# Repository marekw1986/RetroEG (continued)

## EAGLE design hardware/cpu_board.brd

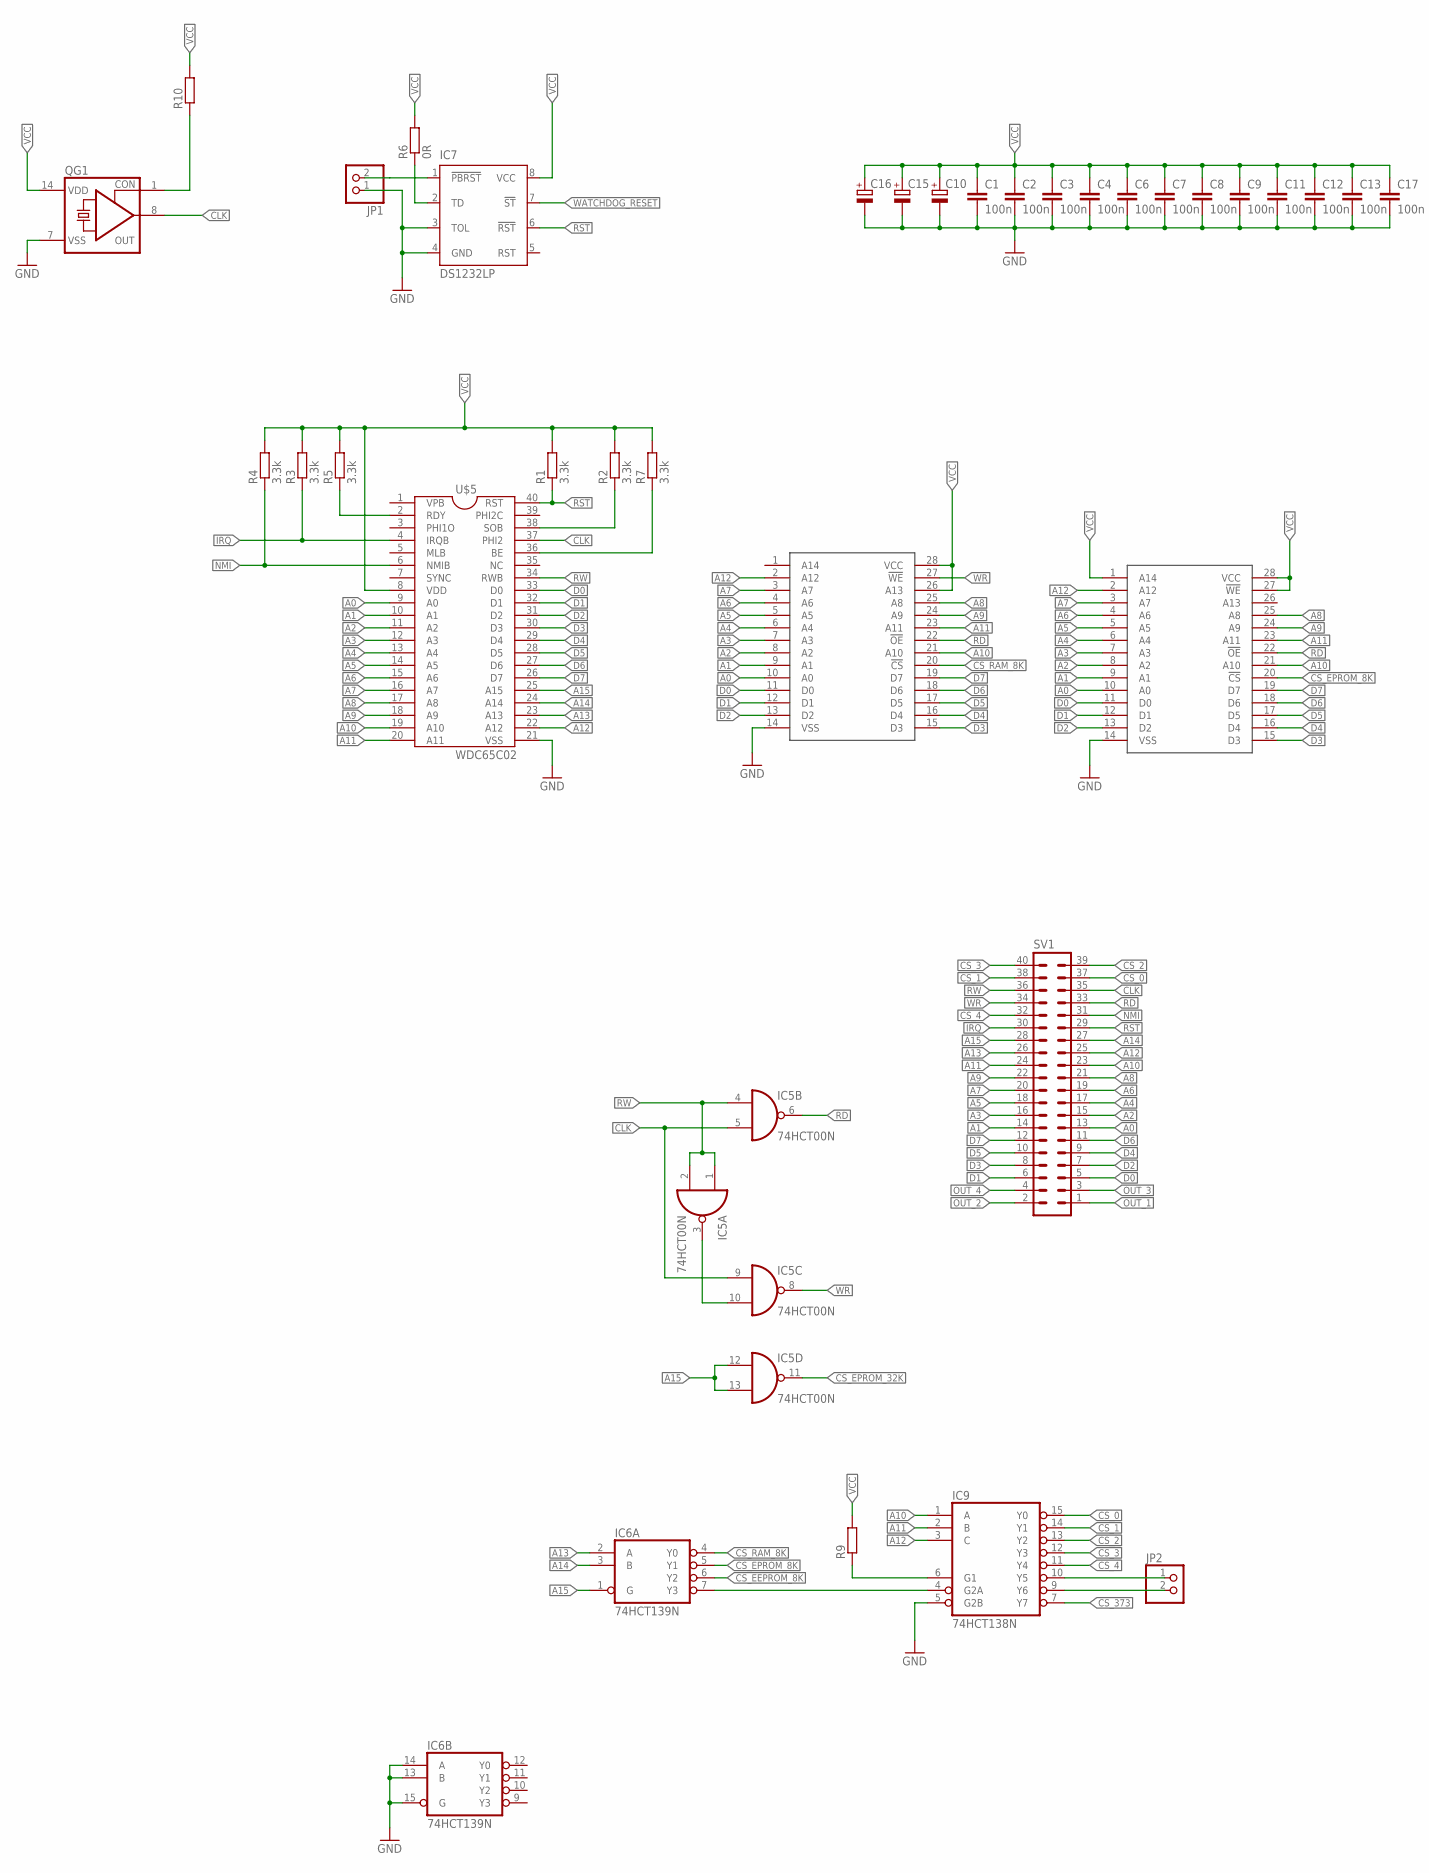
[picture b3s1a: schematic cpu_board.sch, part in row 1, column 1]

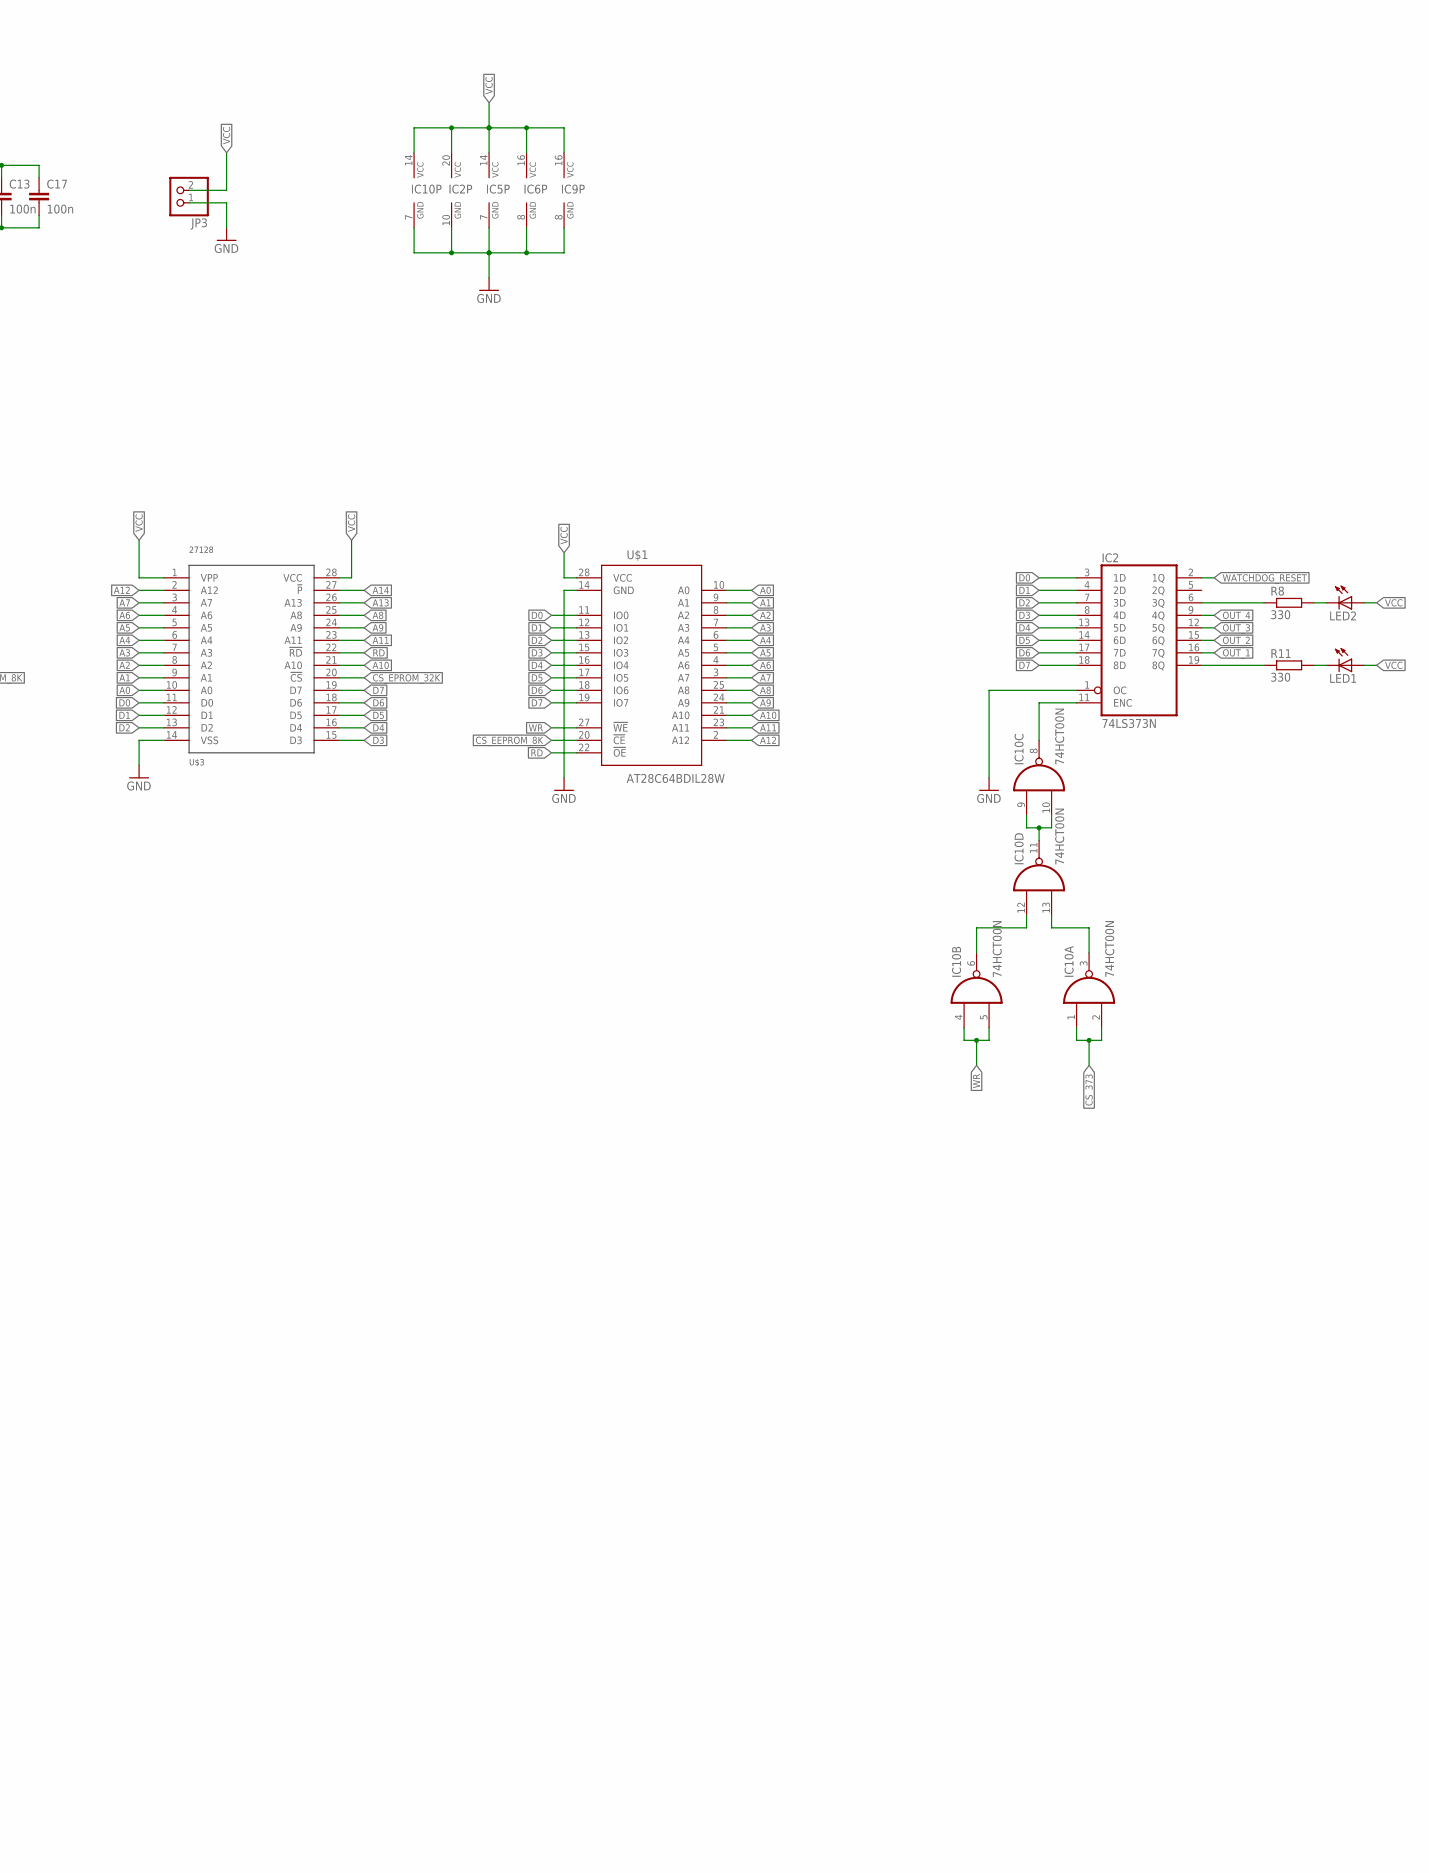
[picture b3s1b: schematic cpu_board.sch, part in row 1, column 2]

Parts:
C1, C2, C3, C4, C6, C7, C8, C9, C17: 100n; C1206
C10: CPOL-EUE5-10.5; E5-10,5
C11, C12, C13: 100n; C0805
C15, C16: CPOL-EUSMCB; SMC_B
IC2: 74LS373N; DIL20
IC5, IC10: 74HCT00N; DIL14
IC6: 74HCT139N; DIL16
IC7: DS1232LP; DIL08
IC9: 74HCT138N; DIL16
JP1, JP2: PINHD-1X2; 1X02
JP3: PINHD-1X2/90; 1X02/90
LED1, LED2: LED5MM
QG1: CRYSTAL_RES-SG51; SG51
R1, R2, R3, R4, R5, R7: 3.3k; R1206
R6: 0R; R1206
R8, R11: 330; R1206
R9: R-EU_0204/7; 0204/7
R10: R-EU_R1206; R1206
SV1: ML40L
U$1: AT28C64BDIL28W; DIL28-6
U$2, U$4: 62256; DIL28-6
U$3: 27128; DIL28
U$5: WDC65C02; DIL40

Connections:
A0: SV1.13, U$1.10 (A0), U$2.10 (A0), U$3.10 (A0), U$4.10 (A0), U$5.9 (A0)
A1: SV1.14, U$1.9 (A1), U$2.9 (A1), U$3.9 (A1), U$4.9 (A1), U$5.10 (A1)
A2: SV1.15, U$1.8 (A2), U$2.8 (A2), U$3.8 (A2), U$4.8 (A2), U$5.11 (A2)
A3: SV1.16, U$1.7 (A3), U$2.7 (A3), U$3.7 (A3), U$4.7 (A3), U$5.12 (A3)
A4: SV1.17, U$1.6 (A4), U$2.6 (A4), U$3.6 (A4), U$4.6 (A4), U$5.13 (A4)
A5: SV1.18, U$1.5 (A5), U$2.5 (A5), U$3.5 (A5), U$4.5 (A5), U$5.14 (A5)
A6: SV1.19, U$1.4 (A6), U$2.4 (A6), U$3.4 (A6), U$4.4 (A6), U$5.15 (A6)
A7: SV1.20, U$1.3 (A7), U$2.3 (A7), U$3.3 (A7), U$4.3 (A7), U$5.16 (A7)
A8: SV1.21, U$1.25 (A8), U$2.25 (A8), U$3.25 (A8), U$4.25 (A8), U$5.17 (A8)
A9: SV1.22, U$1.24 (A9), U$2.24 (A9), U$3.24 (A9), U$4.24 (A9), U$5.18 (A9)
A10: IC9.1 (A), SV1.23, U$1.21 (A10), U$2.21 (A10), U$3.21 (A10), U$4.21 (A10), U$5.19 (A10)
A11: IC9.2 (B), SV1.24, U$1.23 (A11), U$2.23 (A11), U$3.23 (A11), U$4.23 (A11), U$5.20 (A11)
A12: IC9.3 (C), SV1.25, U$1.2 (A12), U$2.2 (A12), U$3.2 (A12), U$4.2 (A12), U$5.22 (A12)
A13: IC6.2 (A), SV1.26, U$3.26 (A13), U$5.23 (A13)
A14: IC6.3 (B), SV1.27, U$3.27 (!P), U$5.24 (A14)
A15: IC5.12 (I0), IC5.13 (I1), IC6.1 (G), SV1.28, U$5.25 (A15)
CLK: IC5.5 (I1), IC5.9 (I0), QG1.8 (OUT), SV1.35, U$5.37 (PHI2)
CS_0: IC9.15 (Y0), SV1.37
CS_1: IC9.14 (Y1), SV1.38
CS_2: IC9.13 (Y2), SV1.39
CS_3: IC9.12 (Y3), SV1.40
CS_4: IC9.11 (Y4), SV1.32
CS_373: IC9.7 (Y7), IC10.1 (I0), IC10.2 (I1)
CS_EEPROM_8K: IC6.6 (Y2), U$1.20 (!CE)
CS_EPROM_8K: IC6.5 (Y1), U$2.20 (!CS)
CS_EPROM_32K: IC5.11 (O), U$3.20 (!CS)
CS_RAM_8K: IC6.4 (Y0), U$4.20 (!CS)
D0: IC2.3 (1D), SV1.5, U$1.11 (IO0), U$2.11 (D0), U$3.11 (D0), U$4.11 (D0), U$5.33 (D0)
D1: IC2.4 (2D), SV1.6, U$1.12 (IO1), U$2.12 (D1), U$3.12 (D1), U$4.12 (D1), U$5.32 (D1)
D2: IC2.7 (3D), SV1.7, U$1.13 (IO2), U$2.13 (D2), U$3.13 (D2), U$4.13 (D2), U$5.31 (D2)
D3: IC2.8 (4D), SV1.8, U$1.15 (IO3), U$2.15 (D3), U$3.15 (D3), U$4.15 (D3), U$5.30 (D3)
D4: IC2.13 (5D), SV1.9, U$1.16 (IO4), U$2.16 (D4), U$3.16 (D4), U$4.16 (D4), U$5.29 (D4)
D5: IC2.14 (6D), SV1.10, U$1.17 (IO5), U$2.17 (D5), U$3.17 (D5), U$4.17 (D5), U$5.28 (D5)
D6: IC2.17 (7D), SV1.11, U$1.18 (IO6), U$2.18 (D6), U$3.18 (D6), U$4.18 (D6), U$5.27 (D6)
D7: IC2.18 (8D), SV1.12, U$1.19 (IO7), U$2.19 (D7), U$3.19 (D7), U$4.19 (D7), U$5.26 (D7)
GND: C1.2, C2.2, C3.2, C4.2, C6.2, C7.2, C8.2, C9.2, C10.-, C11.2, C12.2, C13.2, C15.-, C16.-, C17.2, IC2.1 (OC), IC2.10 (GND), IC5.7 (GND), IC6.8 (GND), IC6.13 (B), IC6.14 (A), IC6.15 (G), IC7.3 (TOL), IC7.4 (GND), IC9.5 (G2B), IC9.8 (GND), IC10.7 (GND), JP1.1, JP3.1, QG1.7 (VSS), U$1.14 (GND), U$2.14 (VSS), U$3.14 (VSS), U$4.14 (VSS), U$5.21 (VSS)
IRQ: R3.1, SV1.30, U$5.4 (IRQB)
unnamed: IC7.2 (TD), R6.1
unnamed: R2.1, U$5.38 (SOB)
unnamed: IC7.1 (!PBRST), JP1.2
unnamed: R7.1, U$5.36 (BE)
unnamed: R5.1, U$5.2 (RDY)
unnamed: IC2.19 (8Q), R11.1
unnamed: QG1.1 (CON), R10.1
unnamed: IC6.7 (Y3), IC9.4 (G2A)
unnamed: LED1.K (C), R11.2
unnamed: IC2.11 (ENC), IC10.8 (O)
unnamed: IC10.9 (I0), IC10.10 (I1), IC10.11 (O)
unnamed: IC10.3 (O), IC10.13 (I1)
unnamed: IC10.6 (O), IC10.12 (I0)
unnamed: IC2.6 (3Q), R8.1
unnamed: IC9.10 (Y5), JP2.1
unnamed: LED2.K (C), R8.2
unnamed: IC5.3 (O), IC5.10 (I1)
unnamed: IC9.6 (G1), R9.1
unnamed: IC9.9 (Y6), JP2.2
NMI: R4.1, SV1.31, U$5.6 (NMIB)
OUT_1: IC2.16 (7Q), SV1.1
OUT_2: IC2.15 (6Q), SV1.2
OUT_3: IC2.12 (5Q), SV1.3
OUT_4: IC2.9 (4Q), SV1.4
RD: IC5.6 (O), SV1.33, U$1.22 (!OE), U$2.22 (!OE), U$3.22 (!RD), U$4.22 (!OE)
RST: IC7.6 (!RST), R1.1, SV1.29, U$5.40 (RST)
RW: IC5.1 (I0), IC5.2 (I1), IC5.4 (I0), SV1.36, U$5.34 (RWB)
VCC: C1.1, C2.1, C3.1, C4.1, C6.1, C7.1, C8.1, C9.1, C10.+, C11.1, C12.1, C13.1, C15.+, C16.+, C17.1, IC2.20 (VCC), IC5.14 (VCC), IC6.16 (VCC), IC7.8 (VCC), IC9.16 (VCC), IC10.14 (VCC), JP3.2, LED1.A, LED2.A, QG1.14 (VDD), R1.2, R2.2, R3.2, R4.2, R5.2, R6.2, R7.2, R9.2, R10.2, U$1.28 (VCC), U$2.1 (A14), U$2.27 (!WE), U$2.28 (VCC), U$3.1 (VPP), U$3.28 (VCC), U$4.26 (A13), U$4.28 (VCC), U$5.8 (VDD)
WATCHDOG_RESET: IC2.2 (1Q), IC7.7 (!ST)
WR: IC5.8 (O), IC10.4 (I0), IC10.5 (I1), SV1.34, U$1.27 (!WE), U$4.27 (!WE)

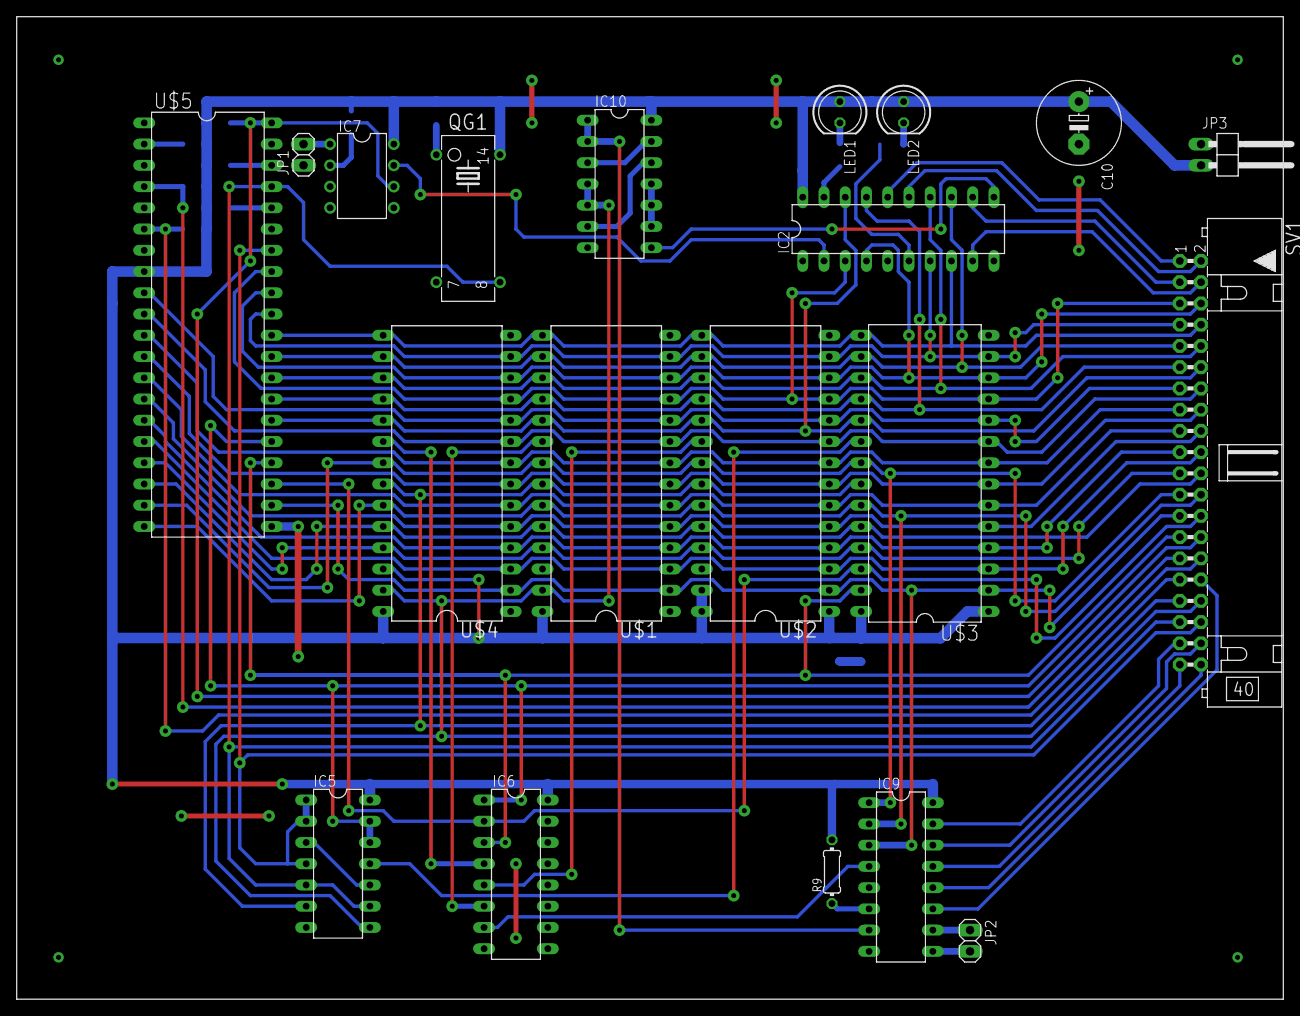
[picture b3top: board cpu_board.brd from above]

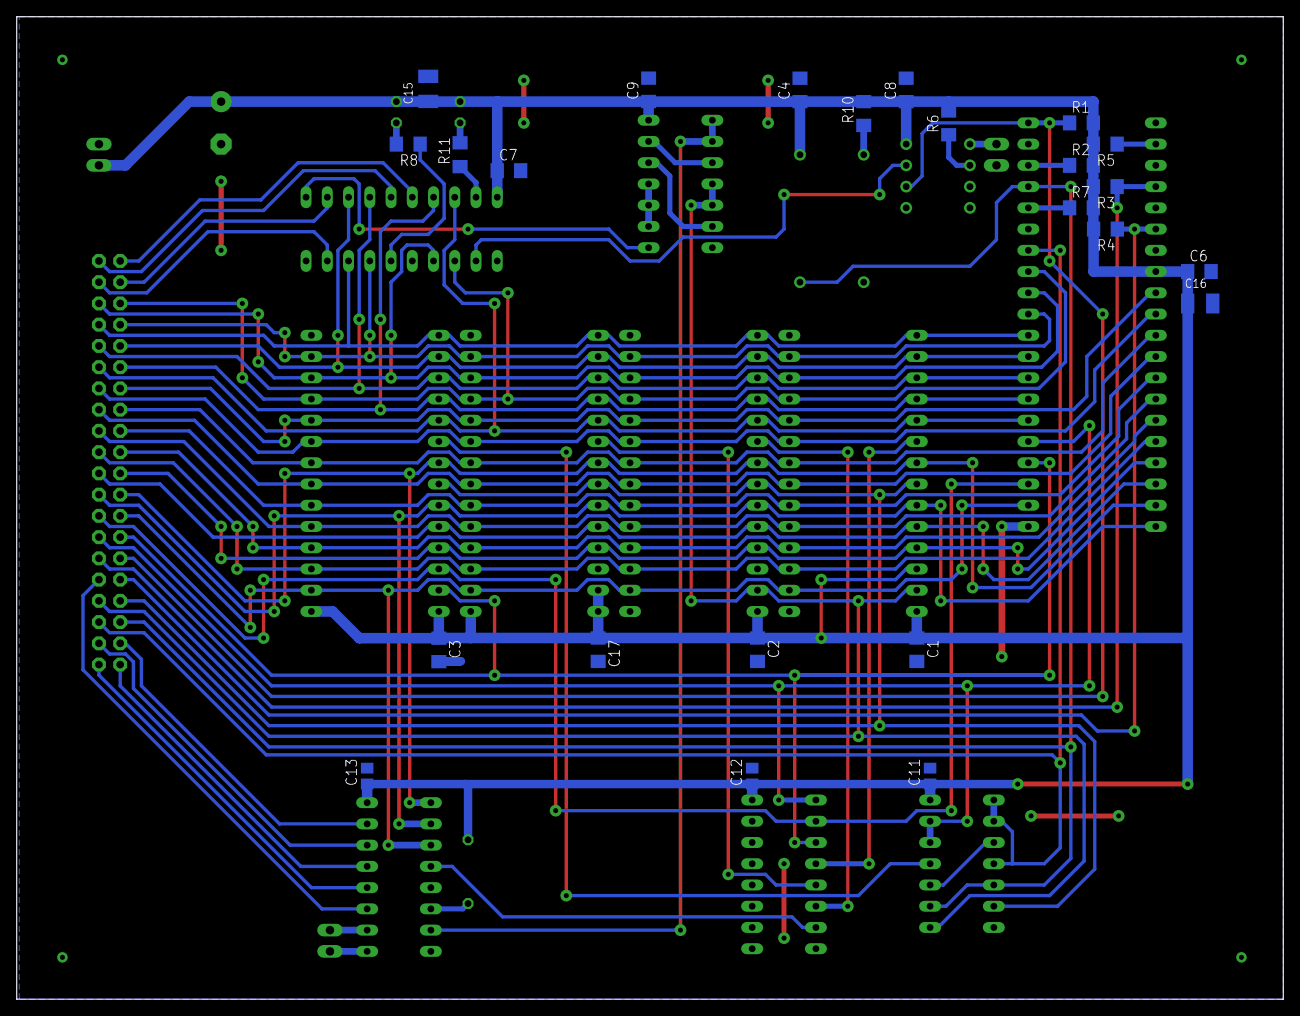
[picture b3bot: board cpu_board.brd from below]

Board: 2 copper layers, 151.4 x 117.5 mm, 44 parts (24 on the bottom side), 67 nets.

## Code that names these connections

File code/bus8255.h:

#ifndef BUS8255_H
#define BUS8255_H

#include <stdint.h>
#include "io.h"

/* Mode 0, Port A = output, Port B = input, Port C = output (unused) */
#define CONF_8255_MODE0_A_OUT_B_IN   0x82

/* ---- Port A bit assignments (open-collector drivers via 7406, inverting) ---- */
#define BIT_PA_1W_OUT   0x08   /* PA3 - 1-Wire bus driver  */
#define BIT_PA_SDA_OUT  0x10   /* PA4 - I2C SDA driver     */
#define BIT_PA_SCL_OUT  0x40   /* PA6 - I2C SCL driver     */

/* ---- Port B bit assignments (bus sense inputs, wired directly to
 * the bus - no buffer, no inversion) ---- */
#define BIT_PB_1W_IN    0x04   /* PB2 - 1-Wire bus sense   */
#define BIT_PB_SDA_IN   0x08   /* PB3 - I2C SDA sense      */

/*
 * Shadow copy of the Port A output latch.
 *
 * PA3/PA4/PA6 drive INVERTING open-collector 7406 buffers, so the
 * *logical* idle state is '0' (driver released, external pull-up
 * holds the bus high) and '1' actively pulls the corresponding bus
 * line low - the opposite of what a non-inverting 7407 would need.
 *
 * We keep a software shadow instead of reading PA_8255 back before
 * every read-modify-write. That avoids ever mixing bits belonging
 * to different buses, and avoids any dependence on whether this
 * particular 8255 part even returns the output latch (rather than
 * the pin state) on a read of an output-configured port.
 */
extern uint8_t porta_shadow;

void bus8255_init(void);

/*
 * Provided elsewhere in your codebase (1MHz 6502, ~16us per call
 * unit). Declared here so onewire.c/i2c_bitbang.c don't need an
 * extra include - delete this line if you'd rather pull the real
 * prototype in from wherever it's already declared.
 */
extern void __fastcall__ delay_16us(uint8_t n);

#endif

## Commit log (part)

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2020-08-23 major changes
2020-08-23 switching state by buttons
2020-08-23 buttons repaired
2020-08-24 minor changes
2020-08-27 README.md updated
2020-09-10 RS485
2020-09-11 CF card fixes
2020-09-11 HD44780 fix
2020-09-18 PCB added
2020-09-19 CF card fix
2020-09-25 testing btn library
2020-09-25 test
2020-09-26 Some changes
2020-09-29 Stability issues resolved
2020-09-29 Some fixes
2020-09-30 Interrupts fixed
2020-09-30 cleaned
2020-10-02 interrupt code optimized
2020-10-03 CF fixes
2020-10-03 CF card fixed
2020-10-05 FatFS added, watchdog changes
2020-10-05 CF changes
2020-10-05 FatFS nd data logging to CF
2020-10-06 uS/h logging added
2020-10-06 Just some fixes
2020-11-18 clear code
2021-03-12 gitignore
2021-03-22 Sound nd timer fixed
2021-03-22 Small changes
2021-03-25 MC6840 code fixed
